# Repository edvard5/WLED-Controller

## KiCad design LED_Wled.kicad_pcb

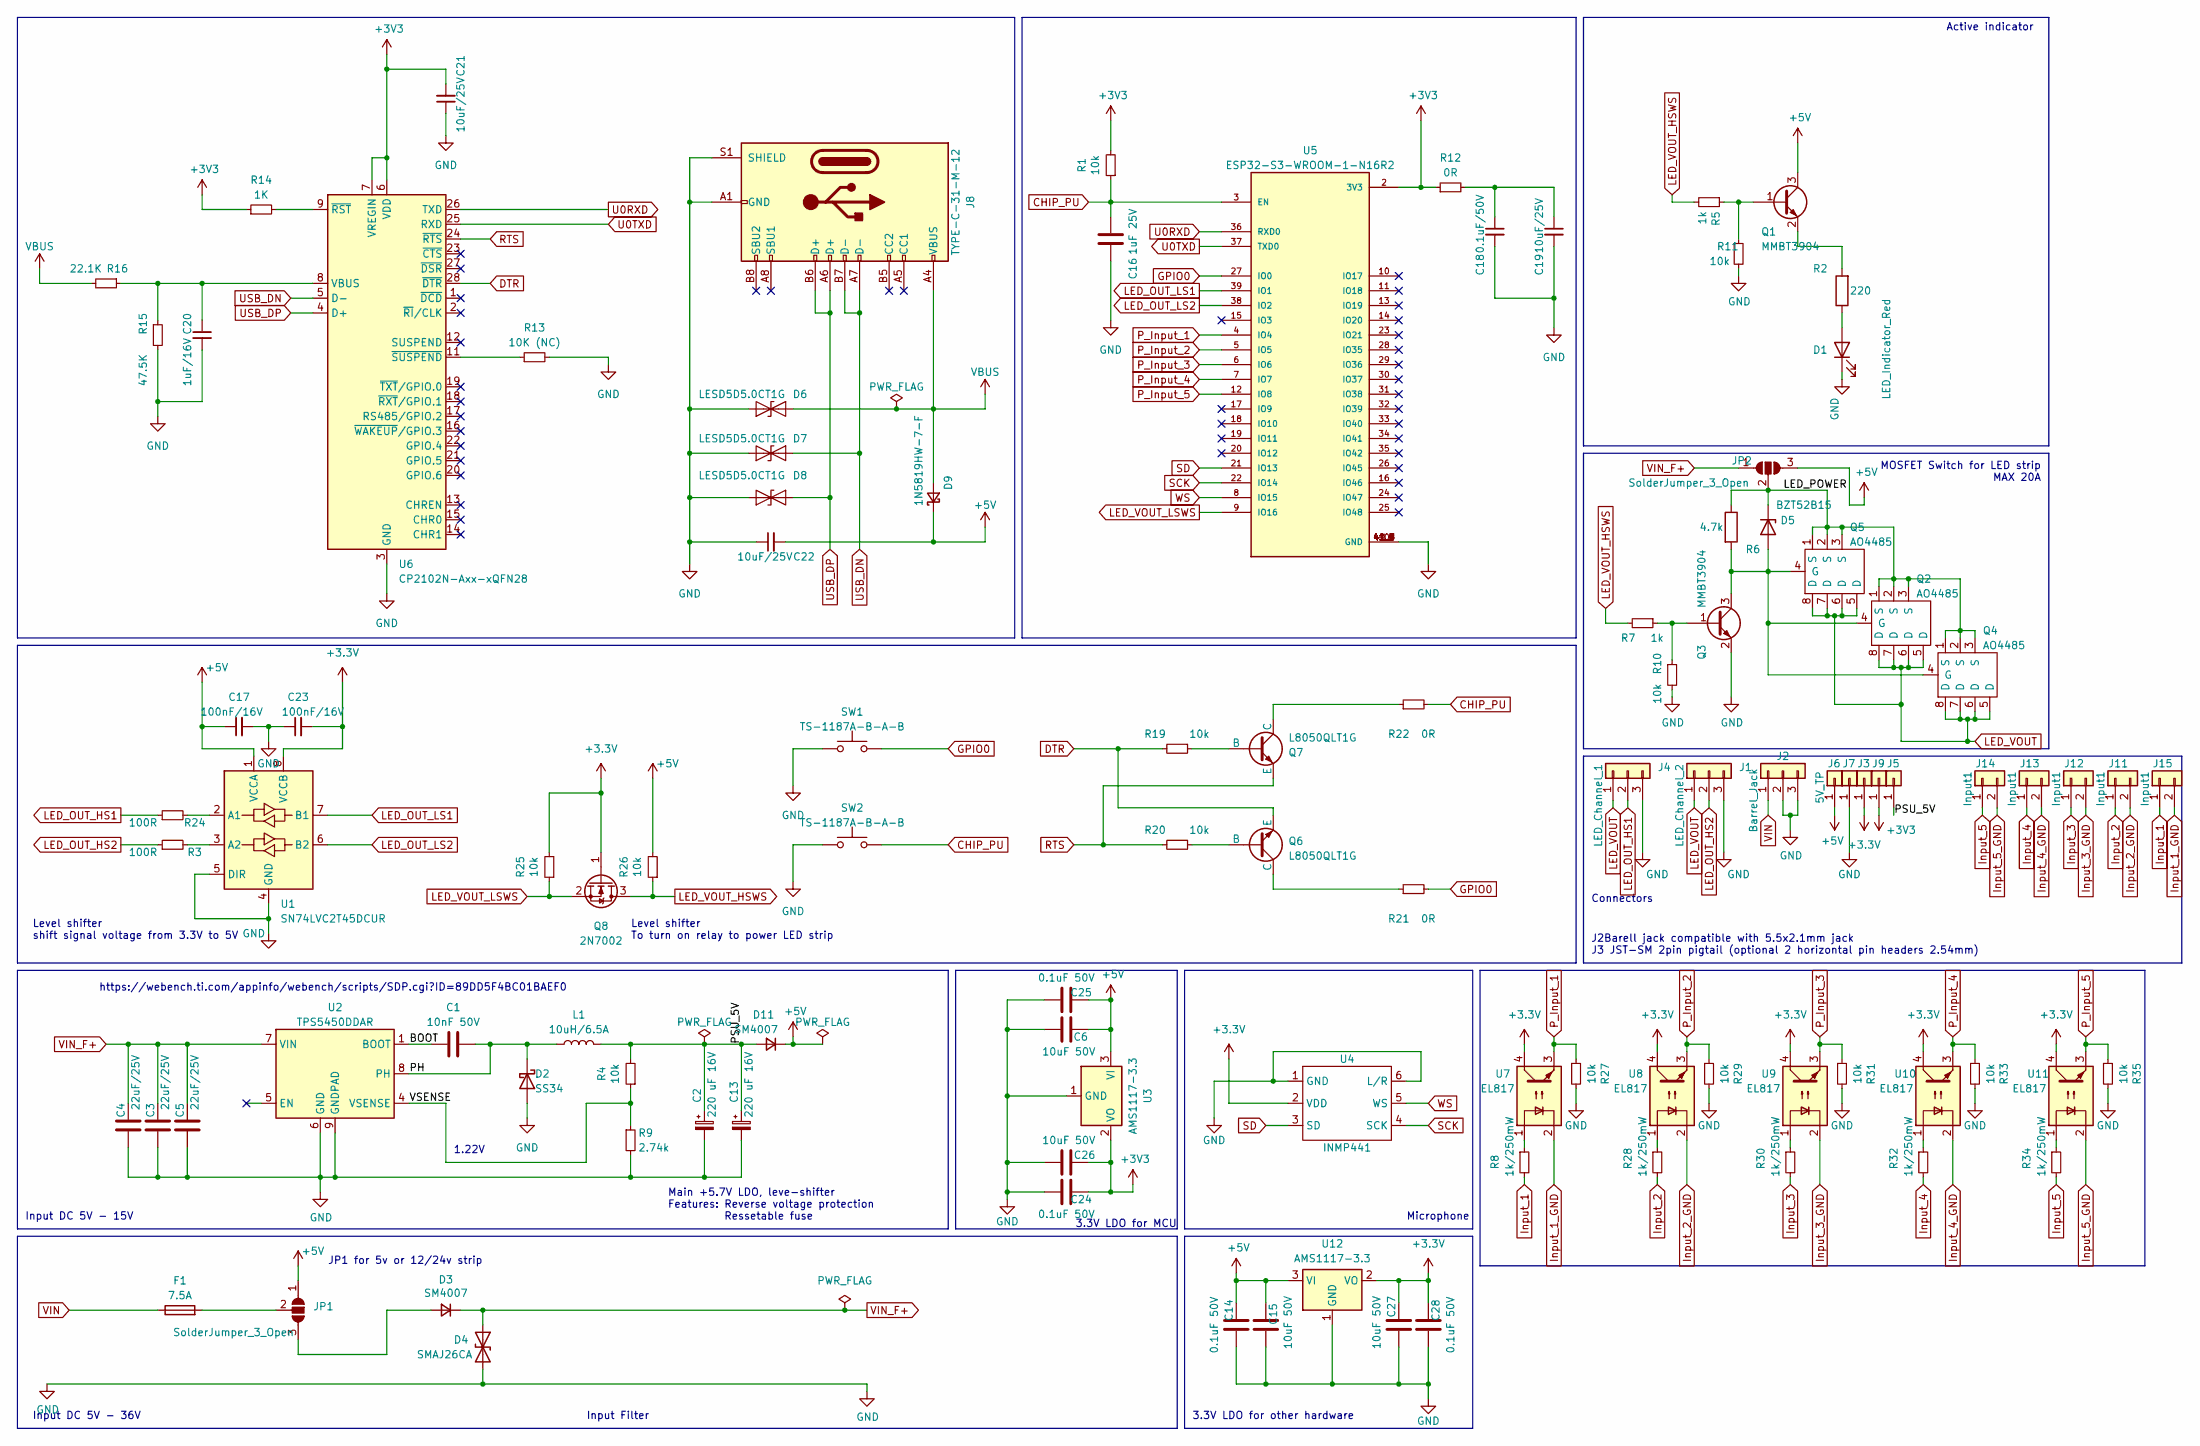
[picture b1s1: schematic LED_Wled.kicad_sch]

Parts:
C1: 10nF 50V; C_0603_1608Metric; MPN 0603B103K500NT; JLCSMT_PKG 0603
C2, C13: 220 uF 16V; CP_Elec_8x6.7; MPN OVZ151M1CTR-0807; JLCSMT C250068
C3, C4, C5: 22uF/25V; C_1206_3216Metric; MPN CL31A226KAHNNNE; JLCSMT C12891
C6, C15, C26, C27: 10uF 50V; C_1206_3216Metric; MPN CL31A106KBHNNNE; JLCSMT C13585
C14, C24, C25, C28: 0.1uF 50V; C_0603_1608Metric; MPN CC0603KRX7R9BB104; JLCSMT C14663
C16: 1uF 25V; C_0402_1005Metric_Pad0.74x0.62mm_HandSolder; MPN CL05A105KA5NQNC; JLCSMT C52923
C17, C23: 100nF/16V; C_0402_1005Metric_Pad0.74x0.62mm_HandSolder
C18: 0.1uF/50V; C_0402_1005Metric_Pad0.74x0.62mm_HandSolder
C19, C21, C22: 10uF/25V; C_0603_1608Metric_Pad1.08x0.95mm_HandSolder
C20: 1uF/16V; C_0402_1005Metric_Pad0.74x0.62mm_HandSolder
D1: LED_Indicator_Red; LED_0805_2012Metric; MPN NCD0805R1; JLCSMT C84256
D2: SS34; D_SMA; MPN SS34; JLCSMT C8678
D3, D11: SM4007; D_SOD-123F; MPN SM4007PL; JLCSMT C64898
D4: SMAJ26CA; D_SMA; MPN SMAJ26CA; JLCSMT C148226
D5: BZT52B15; D_SOD-123; MPN BZT52B15; JLCSMT C179512
D6, D7, D8: LESD5D5.0CT1G; D_SOD-523
D9: 1N5819HW-7-F; D_SOD-123
F1: 7.5A; Fuse_Blade_Mini_directSolder
J1: LED_Channel_2; JST_VH_B3P-VH_1x03_P3.96mm_Vertical; JLC_PART C703273
J2: Barrel_Jack; BarrelJack_Horizontal; MPN DC-005-20A; JLCSMT C136744
J3, J5, J6, J9: Conn_01x01; TestPoint_Pad_1.5x1.5mm
J4: LED_Channel_1; JST_VH_B3P-VH_1x03_P3.96mm_Vertical; JLC_PART C703273
J7: 5V_TP; TestPoint_Pad_1.5x1.5mm
J8: TYPE-C-31-M-12; USB_C_Receptacle_G-Switch_GT-USB-7010ASV; JLCPCB_PART C165948
J11, J12, J13, J14, J15: Input1; JST_XH_B2B-XH-AM_1x02_P2.50mm_Vertical; JLC_PART C692532
JP1, JP2: SolderJumper_3_Open; SolderJumper-3_P2.0mm_Open_TrianglePad1.0x1.5mm_NumberLabels
L1: 10uH/6.5A; L_Wuerth_WE-PD2-Typ-XL; MPN BMRF00101040100MA1; JLCSMT C2903677
Q1, Q3: MMBT3904; SOT-23; MPN MMBT3904; JLCSMT C20526
Q2, Q4, Q5: AO4485; SOIC-8_3.9x4.9mm_P1.27mm; MPN AO4485; JLCSMT C51499
Q6, Q7: L8050QLT1G; SOT-23
Q8: 2N7002; SOT-23
R1, R4, R10, R11, R19, R20, R25, R26, R27, R29, R31, R33, R35: 10k; R_0805_2012Metric; MPN 0805W8F1002T5E; JLCSMT C17414
R2: 220; R_0603_1608Metric
R3, R24: 100R; R_0805_2012Metric
R5, R7: 1k; R_0603_1608Metric; MPN 0603WAF2401T5E; JLCSMT C22940
R6: 4.7k; R_0603_1608Metric; MPN 0603WAF4701T5E; JLCSMT_PKG 0603
R8, R28, R30, R32, R34: 1k/250mW; R_1206_3216Metric_Pad1.30x1.75mm_HandSolder; JLC_PART C4410
R9: 2.74k; R_0603_1608Metric
R12, R21, R22: 0R; R_0805_2012Metric
R13: 10K (NC); R_0805_2012Metric
R14: 1K; R_0805_2012Metric
R15: 47.5K; R_0805_2012Metric
R16: 22.1K; R_0805_2012Metric
SW1, SW2: TS-1187A-B-A-B; SW_Push_1P1T_XKB_TS-1187A; JLC_PART C318884
U1: SN74LVC2T45DCUR; VSSOP-8_2.4x2.1mm_P0.5mm
U2: TPS5450DDAR; TI_SO-PowerPAD-8; MPN TPS5450DDAR; JLCSMT C114425
U3, U12: AMS1117-3.3; SOT-223-3_TabPin2; MPN AMS1117-3.3; JLCSMT C6186
U4: INMP441
U5: ESP32-S3-WROOM-1-N16R2; XCVR_ESP32-S3-WROOM-1-N16R2; PARTREV v1.0
U6: CP2102N-Axx-xQFN28; QFN-28-1EP_5x5mm_P0.5mm_EP3.35x3.35mm
U7, U8, U9, U10, U11: EL817; DIP-4_W7.62mm; JLC_PART C106900

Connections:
+3.3V: C23.2, C27.1, C28.2, J3.1, Q8.1 (G), R25.2, U1.8 (VCCB), U4.2 (VDD), U7.4, U8.4, U9.4, U10.4, U11.4, U12.2 (VO)
+3V3: C21.2, C24.2, C26.1, J9.1, R1.2, R12.1, R14.1, U3.2 (VO), U5.2 (3V3), U6.6 (VDD), U6.7 (VREGIN)
+5V: C6.1, C14.2, C15.1, C17.1, C22.2, C25.2, D9.1 (K), D11.1 (K), J6.1, JP1.1 (A), JP2.3 (B), Q1.3 (C), R26.2, U1.1 (VCCA), U3.3 (VI), U12.3 (VI)
/BOOT: C1.2, U2.1 (BOOT)
/LED_POWER: D5.1 (K), JP2.2 (C), Q2.1 (S), Q2.2 (S), Q2.3 (S), Q4.1 (S), Q4.2 (S), Q4.3 (S), Q5.1 (S), Q5.2 (S), Q5.3 (S), R6.1
/PH: C1.1, D2.1 (K), L1.1, U2.8 (PH)
/PSU_5V: C2.1, C13.1, D11.2 (A), J5.1, L1.2, R4.2
/VSENSE: R4.1, R9.1, U2.4 (VSENSE)
CHIP_PU: C16.2, R1.1, R22.2, SW2.2, U5.3 (EN)
DTR: Q6.3 (E), R19.2, U6.28 (~DTR)
GND: C2.2, C3.1, C4.1, C5.1, C6.2, C13.2, C14.1, C15.2, C16.1, C17.2, C18.2, C19.2, C20.2, C21.1, C22.1, C23.1, C24.1, C25.1, C26.2, C27.2, C28.1, D1.1 (K), D2.2 (A), D4.2 (A2), D6.1 (A1), D7.1 (A1), D8.1 (A1), J1.3, J2.2, J2.3, J4.3, J7.1, J8.A1 (GND), J8.A12 (GND), J8.B1 (GND), J8.B12 (GND), J8.S1 (SHIELD), Q3.2 (E), R9.2, R10.2, R11.2, R13.2, R15.2, R27.2, R29.2, R31.2, R33.2, R35.2, SW1.1, SW2.1, U1.4 (GND), U1.5 (DIR), U2.6 (GND), U2.9 (GNDPAD), U3.1 (GND), U4.1 (GND), U4.6 (L/R), U5.1 (GND), U5.40 (GND), U5.41_1 (GND), U5.41_2 (GND), U5.41_3 (GND), U5.41_4 (GND), U5.41_5 (GND), U5.41_6 (GND), U5.41_7 (GND), U5.41_8 (GND), U5.41_9 (GND), U5.41_10, U5.41_11, U5.41_12, U5.41_13, U5.41_14, U5.41_15, U5.41_16, U5.41_17, U5.41_18, U5.41_19, U5.41_20, U5.41_21, U6.3 (GND), U6.29 (GND), U12.1 (GND)
GPIO0: R21.2, SW1.2, U5.27 (IO0)
Input_1: J15.1, R8.2
Input_1_GND: J15.2, U7.2
Input_2: J11.1, R28.2
Input_2_GND: J11.2, U8.2
Input_3: J12.1, R30.2
Input_3_GND: J12.2, U9.2
Input_4: J13.1, R32.2
Input_4_GND: J13.2, U10.2
LED_OUT_HS1: J4.2, R24.1
LED_OUT_HS2: J1.2, R3.1
LED_OUT_LS1: U1.7 (B1), U5.39 (IO1)
LED_OUT_LS2: U1.6 (B2), U5.38 (IO2)
LED_VOUT: J1.1, J4.1, Q2.5 (D), Q2.6 (D), Q2.7 (D), Q2.8 (D), Q4.5 (D), Q4.6 (D), Q4.7 (D), Q4.8 (D), Q5.5 (D), Q5.6 (D), Q5.7 (D), Q5.8 (D)
LED_VOUT_HSWS: Q8.3 (D), R5.2, R7.2, R26.1
LED_VOUT_LSWS: Q8.2 (S), R25.1, U5.9 (IO16)
unnamed: C18.1, C19.1, R12.2
unnamed: D1.2 (A), R2.1
unnamed: D3.2 (A), JP1.3 (B)
unnamed: D5.2 (A), Q2.4 (G), Q3.3 (C), Q4.4 (G), Q5.4 (G), R6.2
unnamed: J14.1, R34.2
unnamed: J14.2, U11.2
unnamed: F1.2, JP1.2 (C)
unnamed: Q1.1 (B), R5.1, R11.1
unnamed: Q1.2 (E), R2.2
unnamed: Q3.1 (B), R7.1, R10.1
unnamed: Q6.2 (B), R20.1
unnamed: Q6.1 (C), R21.1
unnamed: Q7.2 (B), R19.1
unnamed: Q7.1 (C), R22.1
unnamed: R8.1, U7.1
unnamed: R28.1, U8.1
unnamed: R30.1, U9.1
unnamed: R32.1, U10.1
unnamed: R34.1, U11.1
unnamed: R35.1, U5.12 (IO8), U11.3
unnamed: R24.2, U1.2 (A1)
unnamed: R3.2, U1.3 (A2)
unnamed: C20.1, R15.1, R16.1, U6.8 (VBUS)
unnamed: R14.2, U6.9 (~RST)
unnamed: R13.1, U6.11 (~SUSPEND)
P_Input_1: R27.1, U5.4 (IO4), U7.3
P_Input_2: R29.1, U5.5 (IO5), U8.3
P_Input_3: R31.1, U5.6 (IO6), U9.3
P_Input_4: R33.1, U5.7 (IO7), U10.3
RTS: Q7.3 (E), R20.2, U6.24 (~RTS)
SCK: U4.4 (SCK), U5.22 (IO14)
SD: U4.3 (SD), U5.21 (IO13)
U0RXD: U5.36 (RXD0), U6.26 (TXD)
U0TXD: U5.37 (TXD0), U6.25 (RXD)
USB_DN: D7.2 (A2), J8.A7 (D-), J8.B7 (D-), U6.5 (D-)
USB_DP: D8.2 (A2), J8.A6 (D+), J8.B6 (D+), U6.4 (D+)
VBUS: D6.2 (A2), D9.2 (A), J8.A4 (VBUS), J8.A9 (VBUS), J8.B4 (VBUS), J8.B9 (VBUS), R16.2
VIN: F1.1, J2.1
VIN_F+: C3.2, C4.2, C5.2, D3.1 (K), D4.1 (A1), JP2.1 (A), U2.7 (VIN)
WS: U4.5 (WS), U5.8 (IO15)

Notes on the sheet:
Microphone
3.3V LDO for other hardware
Main +5.7V LDO, leve-shifter Features: Reverse voltage protection Ressetable fuse
Level shifter shift signal voltage from 3.3V to 5V
Input Filter
Level shifter To turn on relay to power LED strip
Active indicator
J2Barell jack compatible with 5.5x2.1mm jack J3 JST-SM 2pin pigtail (optional 2 horizontal pin headers 2.54mm)
1.22V
MOSFET Switch for LED strip MAX 20A
Input DC 5V - 36V
Connectors
3.3V LDO for MCU
https://webench.ti.com/appinfo/webench/scripts/SDP.cgi?ID=89DD5F4BC01BAEF0
Input DC 5V - 15V
JP1 for 5v or 12/24v strip

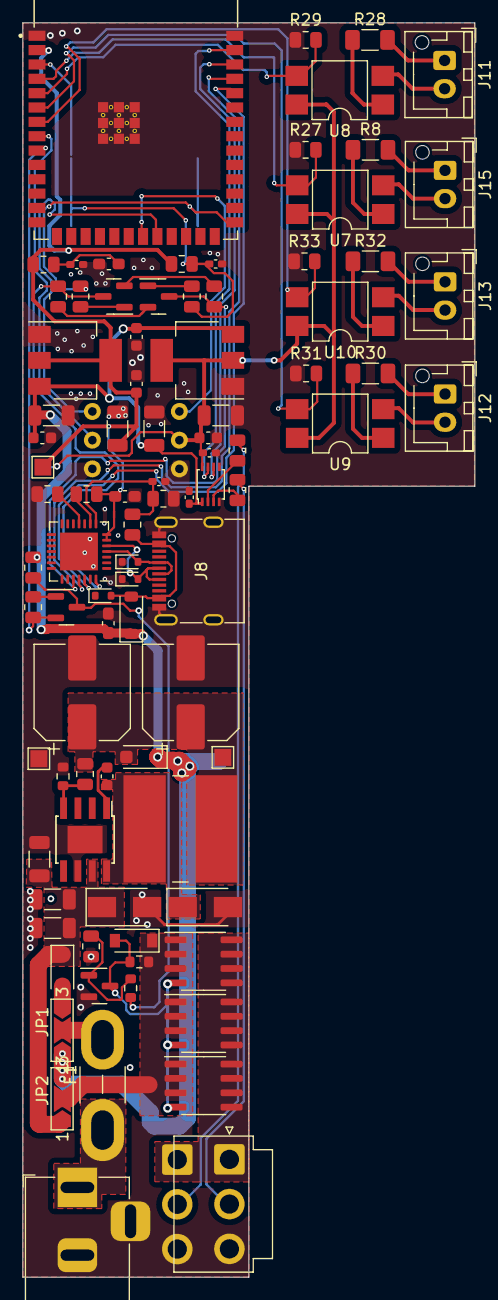
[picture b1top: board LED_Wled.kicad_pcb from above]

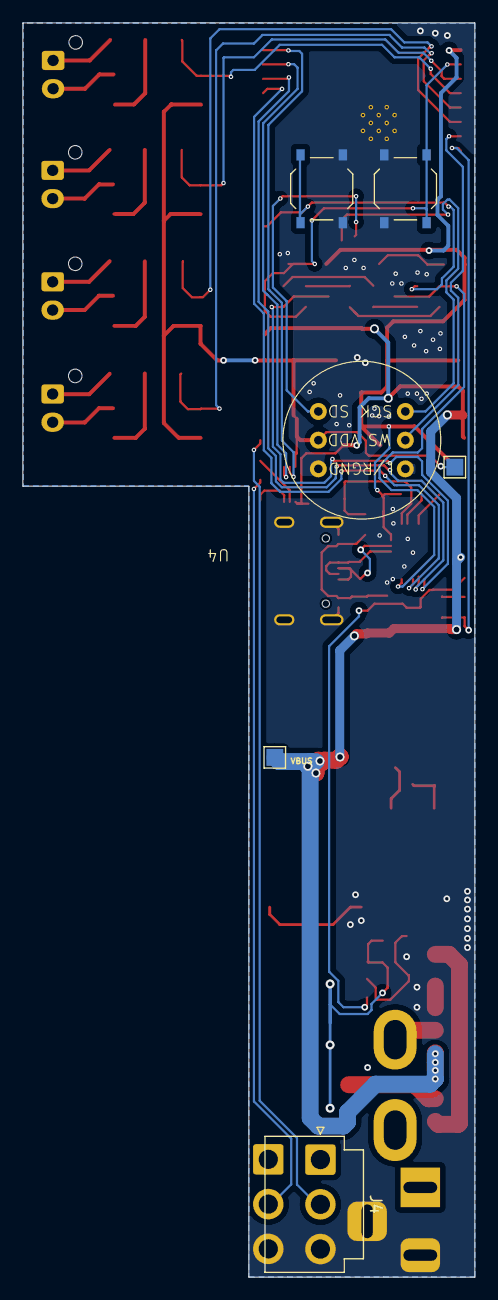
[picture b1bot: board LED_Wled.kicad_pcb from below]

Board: 2 copper layers, 40.0 x 111.0 mm, 95 parts (6 on the bottom side), 60 nets.

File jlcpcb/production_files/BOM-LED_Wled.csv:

Comment,Designator,Footprint,LCSC
EL817,"U10,U7,U8,U9",SMDIP-4_W7.62mm,C106900
TPS5450DDAR,U2,TI_SO-PowerPAD-8,C114425
22uF/25V,"C3,C4,C5",C_1206_3216Metric,C12891
2.74k,R9,R_0603_1608Metric,C13167
10uF 50V,"C15,C26,C27,C6",C_1206_3216Metric,C13585
Barrel_Jack,J2,BarrelJack_Horizontal,C136744
0.1uF 50V,"C14,C24,C25,C28",C_0603_1608Metric,C14663
P6SSMAJ33CA,D4,D_SMA,C148226
100nF/16V,"C17,C23",C_0402_1005Metric_Pad0.74x0.62mm_HandSolder,C1525
TYPE-C-31-M-12,J8,USB_C_Receptacle_G-Switch_GT-USB-7010ASV,C165948
100R,"R24,R3",R_0805_2012Metric,C17408
10k,"R1,R10,R16,R19,R20,R25,R26,R27,R29,R31,R33,R4",R_0805_2012Metric,C17414
0R,"R12,R21,R22",R_0805_2012Metric,C17477
1K,R14,R_0805_2012Metric,C17513
22k,R15,R_0805_2012Metric,C17560
BZT52B15,D5,D_SOD-123,C179512
MMBT3904,Q3,SOT-23,C20526
SN74LVC2T45DCUR,U1,VSSOP-8_2.4x2.1mm_P0.5mm,C22672
1k,R7,R_0603_1608Metric,C22940
4.7k,R6,R_0603_1608Metric,C23162
220 uF 16V,"C13,C2",CP_Elec_8x6.7,C250068
10uH/6.5A,L1,L_Wuerth_WE-PD2-Typ-XL,C2903677
ESP32-S3-WROOM-1-N16R2,U5,XCVR_ESP32-S3-WROOM-1-N16R2,C2913205
0.1uF/50V,C18,C_0402_1005Metric_Pad0.74x0.62mm_HandSolder,C307331
TS-1187A-B-A-B,"SW1,SW2",SW_Push_1P1T_XKB_TS-1187A,C318884
1k/250mW,"R28,R30,R32,R8",R_1206_3216Metric_Pad1.30x1.75mm_HandSolder,C4410
AO4485,"Q2,Q4,Q5",SOIC-8_3.9x4.9mm_P1.27mm,C51499
LESD5D5.0CT1G,"D6,D7,D8",D_SOD-523,C5199850
1uF 25V,"C16,C20",C_0402_1005Metric_Pad0.74x0.62mm_HandSolder,C52923
10nF 50V,C1,C_0603_1608Metric,C57112
AMS1117-3.3,"U12,U3",SOT-223-3_TabPin2,C6186
SM4007,"D11,D3",D_SOD-123F,C64898
S9013 J3,"Q6,Q7",SOT-23,C6749
Input1,"J11,J12,J13,J15",JST_XH_B2B-XH-AM_1x02_P2.50mm_Vertical,C692532
LED_Channel_2,"J1,J4",JST_VH_B3P-VH_1x03_P3.96mm_Vertical,C703273
1N5819HW-7-F,D9,D_SOD-123,C82544
2N7002,Q8,SOT-23,C8545
SS34,D2,D_SMA,C8678
10uF/25V,"C19,C21,C22",C_0603_1608Metric_Pad1.08x0.95mm_HandSolder,C96446
CP2102N-Axx-xQFN28,U6,QFN-28-1EP_5x5mm_P0.5mm_EP3.35x3.35mm,C964632
Conn_01x01,J5,TestPoint_Pad_1.5x1.5mm,
SolderJumper_3_Open,JP2,SolderJumper-3_P2.0mm_Open_TrianglePad1.0x1.5mm_NumberLabels,
INMP441,U4,INMP441,
5V_TP,J7,TestPoint_Pad_1.5x1.5mm,
10K (NC),R13,R_0805_2012Metric,
SolderJumper_3_Open,JP1,SolderJumper-3_P2.0mm_Open_TrianglePad1.0x1.5mm_NumberLabels,
Conn_01x01,J9,TestPoint_Pad_1.5x1.5mm,
Conn_01x01,J3,TestPoint_Pad_1.5x1.5mm,
7.5A,F1,Fuse_Blade_Mini_directSolder,
Conn_01x01,J6,TestPoint_Pad_1.5x1.5mm,

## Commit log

2022-07-20 init v2
2022-07-21 pcb drawn, changed components
    lm1117 to ams1117
2022-07-22 Rename main.yml to github-cli.yml
2022-07-22 test
2022-07-22 connector changes, pcb redesign
    added +5V output with switch with mosfet, changed level shifter from transistor to buffer 4chan, added 2 more led strip channels
2022-07-22 redrawn pcb from scratch rev2.0
2022-11-16 fixed +5v rail switch
2023-01-06 migration to kicad 6
2023-01-25 updated parts, rdy for production?
2023-02-01 rev2.01
2023-07-27 rev2.1.0 WIP
2023-07-27 added couple of footprints
2023-07-28 PCB design WIP
2023-07-31 removed power indicator LED, replaced some parts to basic
